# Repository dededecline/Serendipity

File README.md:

# Serendipity

## Board Details
Serendipity is a collaboration between [dededecline](https://github.com/dededecline) and [liv](https://github.com/ojthetiny)

Photos by group buy participants can be found [here!](https://imgur.com/a/I6LpYkj)

More info can be found on the [Geekhack interest check.](https://geekhack.org/index.php?topic=119558)

## Hardware
* **Back Case Screws:** [4x m3x14mm](https://www.mcmaster.com/92832A566)
* **Front Case Screws:** [4x m3x8mm](https://www.mcmaster.com/90991A113)
* **Weight Screws:** [2x m3x5mm countersunk](https://www.mcmaster.com/90236A118)
* **Plate Screws:** [8x m3x8mm](https://www.mcmaster.com/90991A113)
* **Badge Screws:** [2x m2x5mm](https://www.mcmaster.com/90236A103)
* **DB Screws:** [4x m2x5mm](https://www.mcmaster.com/90236A103)
* **O-Rings:** [16x 1.5mmx2.5mm, 70 duro recommended](https://www.theoringstore.com/store/index.php?main_page=product_info&products_id=1817)
* **Feet:** [2x Geonworks 60% feet](https://geon.works/products/feet-284)

## Additional Information
The o-rings *are required* for the build to work properly. For each plate screw, one o-ring goes between the top case piece and the plate, and another goes between the plate and the screw head. Do not overly tighten plate screws.

All files required for manufacturing are present in this repository.

All relevant information about the board should be in the Geekhack interest check.

## ***DISCLAIMER***
These components have been tested and confirmed to work properly. I am not liable for any issues stemming from usage of these files. Order at your own risk. Support will not be provided, but pull requests will be reviewed and possibly accepted.

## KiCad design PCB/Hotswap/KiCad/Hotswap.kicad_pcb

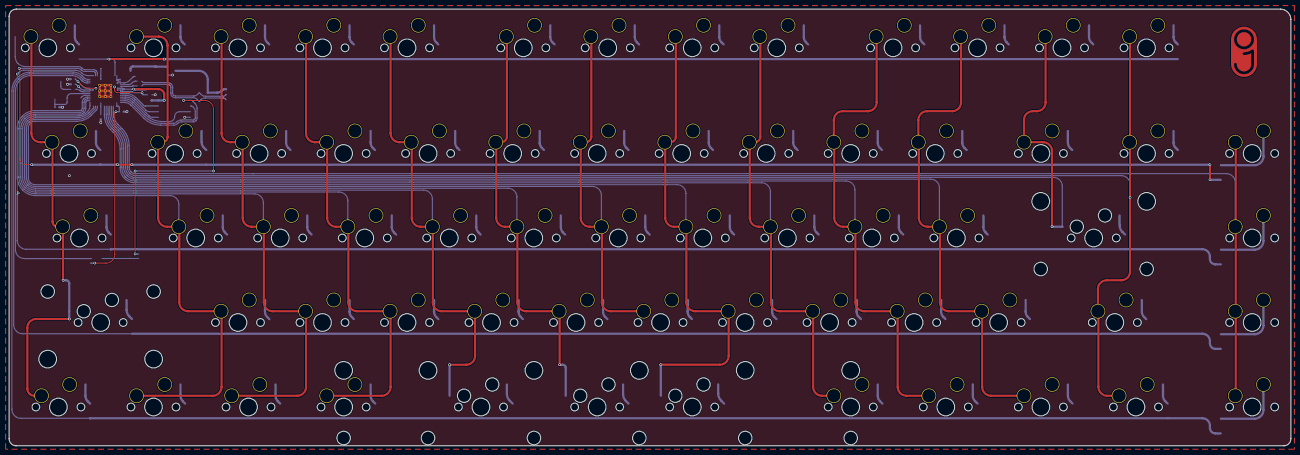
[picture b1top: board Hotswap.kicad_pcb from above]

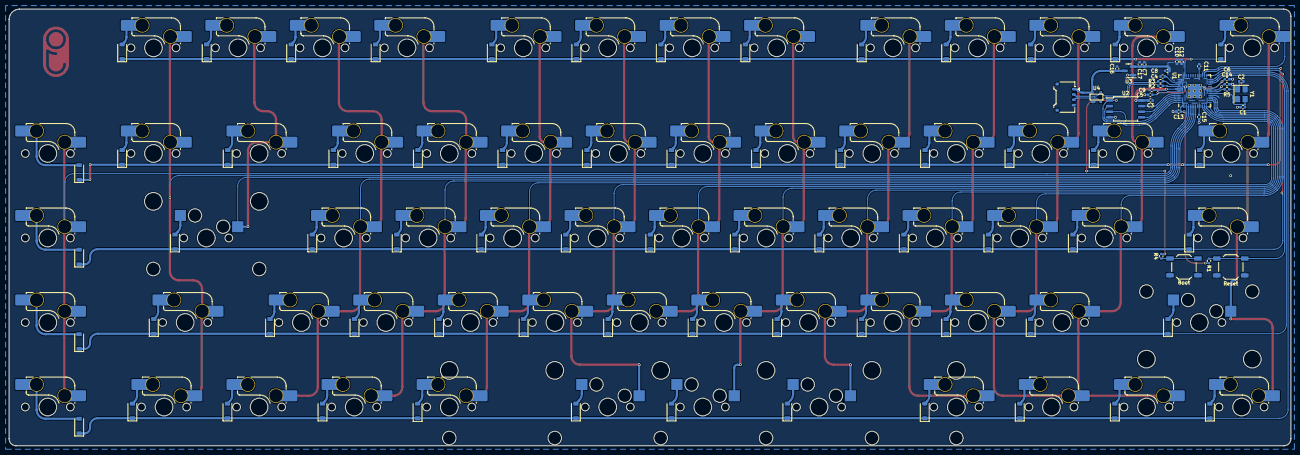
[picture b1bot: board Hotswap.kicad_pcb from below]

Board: 2 copper layers, 288.9 x 98.4 mm, 160 parts (155 on the bottom side), 103 nets.

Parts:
C1, C2: 22pF; C_0402_1005Metric
C3, C5, C6, C9, C10, C11, C12, C13, C14, C15: .1u; C_0402_1005Metric
C4, C8, C16, C17: 1u; C_0402_1005Metric
C7: 10u; C_0402_1005Metric
D1, D2, D3, D4, D5, D6, D7, D8, D9, D10, D11, D12, D13, D14, D15, D16, D17, D18, D19, D20, D21, D22, D23, D24, D25, D26, D27, D28, D29, D30, D31, D32, D33, D34, D35, D36, D37, D38, D39, D40, D41, D42, D43, D44, D45, D46, D47, D48, D49, D50, D51, D52, D53, D54, D55, D56, D57, D58, D59, D60, D61, D62, D63, D64, D65: D_Small; D_SOD-123
J1: EZmate; Molex_Pico-EZmate_78171-0004_1x04-1MP_P1.20mm_Vertical
MX1, MX3, MX7, MX8, MX9, MX10, MX11, MX12, MX13, MX14, MX15, MX16, MX18, MX19, MX20, MX21, MX22, MX23, MX24, MX25, MX27, MX28, MX29, MX30, MX33, MX34, MX35, MX36, MX37, MX38, MX39, MX40, MX42, MX43, MX44, MX45, MX46, MX47, MX48, MX49, MX52, MX53, MX54, MX55, MX56, MX57, MX61, MX65, MX66, MX67, MX68, MX69: MX-NoLED; SW_MX_HS_1u
MX2, MX60: MX-NoLED; SW_MX_HS_1.5u
MX4: MX-NoLED; MXOnly-2.25U-Hotswap
MX5, MX17, MX51, MX64: MX-NoLED; SW_MX_HS_1.25u
MX6, MX63: MX-NoLED; SW_MX_HS_1.75u
MX26, MX59: MX-NoLED; MXOnly-2.25U-Hotswap-ReversedStabilizers
MX31: MX-NoLED; MXOnly-7U-Hotswap-ReversedStabilizers
MX41: MX-NoLED; MXOnly-2.75U-Hotswap-ReversedStabilizers
R1, R4, R5: 1k; R_0402_1005Metric
R2, R3: 27; R_0402_1005Metric
SW1: Boot; SW_SPST_TL3342
SW2: Reset; SW_SPST_TL3342
U1: RP2040; RP2040-QFN-56
U2: W25Q128JVS; SOIC-8_5.23x5.23mm_P1.27mm
U3: XC6206PxxxMR; SOT-23
U4: PRTR5V0U2X; SOT143B
Y1: 12MHz; Crystal_SMD_3225-4Pin_3.2x2.5mm

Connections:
+1V1: C4.1, C5.1, C6.1, U1.23 (DVDD), U1.45 (VREG_VOUT), U1.50 (DVDD)
+3V3: C3.1, C7.1, C8.1, C9.1, C10.1, C11.1, C12.1, C13.1, C14.1, C15.1, C17.1, R1.1, U1.1 (IOVDD), U1.10 (IOVDD), U1.22 (IOVDD), U1.33 (IOVDD), U1.42 (IOVDD), U1.43 (ADC_AVDD), U1.44 (VREG_VIN), U1.48 (USB_VDD), U1.49 (IOVDD), U2.8 (VCC), U3.2 (VO)
+5V: C16.1, J1.1, U3.3 (VI), U4.4 (VCC)
CS: R4.2, U1.56 (QSPI_SS_N), U2.1 (~CS)
D+: J1.3, R2.1, U4.2 (IO1)
D-: J1.2, R3.1, U4.3 (IO2)
GND: C1.1, C2.1, C3.2, C4.2, C5.2, C6.2, C7.2, C8.2, C9.2, C10.2, C11.2, C12.2, C13.2, C14.2, C15.2, C16.2, C17.2, J1.4, SW1.1, SW2.2, U1.19 (TESTEN), U1.57 (GND), U2.4 (GND), U3.1 (GND), U4.1 (GND), Y1.2, Y1.4
unnamed: C2.2, R5.1, Y1.1
unnamed: D1.2 (A), MX1.2 (ROW)
unnamed: D2.2 (A), MX2.2 (ROW)
unnamed: D3.2 (A), MX4.2 (ROW)
unnamed: D4.2 (A), MX5.2 (ROW)
unnamed: D5.2 (A), MX6.2 (COL)
unnamed: D6.2 (A), MX7.2 (ROW)
unnamed: D7.2 (A), MX8.2 (ROW)
unnamed: D8.2 (A), MX9.2 (ROW)
unnamed: D9.2 (A), MX10.2 (ROW)
unnamed: D10.2 (A), MX11.2 (ROW)
unnamed: D11.2 (A), MX12.2 (ROW)
unnamed: D12.2 (A), MX13.2 (ROW)
unnamed: D13.2 (A), MX14.2 (ROW)
unnamed: D14.2 (A), MX15.2 (ROW)
unnamed: D15.2 (A), MX17.2 (COL)
unnamed: D16.2 (A), MX18.2 (ROW)
unnamed: D17.2 (A), MX19.2 (ROW)
unnamed: D18.2 (A), MX20.2 (ROW)
unnamed: D19.2 (A), MX21.2 (ROW)
unnamed: D20.2 (A), MX22.2 (ROW)
unnamed: D21.2 (A), MX23.2 (ROW)
unnamed: D22.2 (A), MX24.2 (ROW)
unnamed: D23.2 (A), MX25.2 (ROW)
unnamed: D24.2 (A), MX26.2 (ROW)
unnamed: D25.2 (A), MX27.2 (ROW)
unnamed: D26.2 (A), MX28.2 (ROW)
unnamed: D27.2 (A), MX29.2 (ROW)
unnamed: D28.2 (A), MX30.2 (ROW)
unnamed: D29.2 (A), MX31.2 (ROW)
unnamed: D30.2 (A), MX33.2 (ROW)
unnamed: D31.2 (A), MX34.2 (ROW)
unnamed: D32.2 (A), MX35.2 (ROW)
unnamed: D33.2 (A), MX36.2 (ROW)
unnamed: D34.2 (A), MX37.2 (ROW)
unnamed: D35.2 (A), MX38.2 (ROW)
unnamed: D36.2 (A), MX39.2 (ROW)
unnamed: D37.2 (A), MX40.2 (ROW)
unnamed: D38.2 (A), MX41.2 (ROW)
unnamed: D39.2 (A), MX42.2 (ROW)
unnamed: D40.2 (A), MX43.2 (ROW)
unnamed: D41.2 (A), MX44.2 (ROW)
unnamed: D42.2 (A), MX45.2 (ROW)
unnamed: D43.2 (A), MX46.2 (ROW)
unnamed: D44.2 (A), MX47.2 (ROW)
unnamed: D45.2 (A), MX48.2 (ROW)
unnamed: D46.2 (A), MX49.2 (ROW)
unnamed: D47.2 (A), MX51.2 (COL)
unnamed: D48.2 (A), MX52.2 (ROW)
unnamed: D49.2 (A), MX53.2 (ROW)
unnamed: D50.2 (A), MX54.2 (ROW)
unnamed: D51.2 (A), MX55.2 (ROW)
unnamed: D52.2 (A), MX56.2 (ROW)
unnamed: D53.2 (A), MX57.2 (ROW)
unnamed: D54.2 (A), MX59.2 (ROW)
unnamed: D55.2 (A), MX60.2 (COL)
unnamed: D56.2 (A), MX61.2 (ROW)
unnamed: D57.2 (A), MX63.2 (ROW)
unnamed: D58.2 (A), MX64.2 (ROW)
unnamed: D59.2 (A), MX65.2 (COL)
unnamed: D60.2 (A), MX66.2 (ROW)
unnamed: D61.2 (A), MX67.2 (ROW)
unnamed: D62.2 (A), MX68.2 (ROW)
unnamed: D63.2 (A), MX69.2 (ROW)
unnamed: D64.2 (A), MX3.2 (ROW)
unnamed: D65.2 (A), MX16.2 (COL)
unnamed: R4.1, SW1.2
unnamed: R2.2, U1.47 (D+)
unnamed: R3.2, U1.46 (D-)
QSPI_CLK: U1.52 (QSPI_SCLK), U2.6 (CLK)
RESET: R1.2, SW2.1, U1.26 (~RUN)
SD0: U1.53 (QSPI_SD0), U2.5 (DI(IO0))
SD1: U1.55 (QSPI_SD1), U2.2 (DO(IO1))
SD2: U1.54 (QSPI_SD2), U2.3 (IO2)
SD3: U1.51 (QSPI_SD3), U2.7 (IO3)
XTAL_IN: C1.2, U1.20 (XTAL_IN), Y1.3
XTAL_OUT: R5.2, U1.21 (XTAL_OUT)
col0: MX1.1 (COL), MX2.1 (COL), MX4.1 (COL), MX5.1 (COL), MX6.1 (ROW), U1.31 (GPIO20)
col1: MX7.1 (COL), MX8.1 (COL), MX9.1 (COL), MX10.1 (COL), MX11.1 (COL), U1.18 (GPIO15)
col2: MX12.1 (COL), MX13.1 (COL), MX14.1 (COL), MX15.1 (COL), MX17.1 (ROW), U1.17 (GPIO14)
col3: MX3.1 (COL), MX18.1 (COL), MX19.1 (COL), MX20.1 (COL), MX21.1 (COL), U1.16 (GPIO13)
col4: MX22.1 (COL), MX23.1 (COL), MX24.1 (COL), MX25.1 (COL), MX26.1 (COL), U1.15 (GPIO12)
col5: MX27.1 (COL), MX28.1 (COL), MX29.1 (COL), MX30.1 (COL), MX31.1 (COL), U1.14 (GPIO11)
col6: MX33.1 (COL), MX34.1 (COL), MX35.1 (COL), MX36.1 (COL), U1.13 (GPIO10)
col7: MX37.1 (COL), MX38.1 (COL), MX39.1 (COL), MX40.1 (COL), MX41.1 (COL), U1.12 (GPIO9)
col8: MX16.1 (ROW), MX42.1 (COL), MX43.1 (COL), MX44.1 (COL), MX45.1 (COL), U1.8 (GPIO6)
col9: MX46.1 (COL), MX47.1 (COL), MX48.1 (COL), MX49.1 (COL), MX51.1 (ROW), U1.7 (GPIO5)
col10: MX52.1 (COL), MX53.1 (COL), MX54.1 (COL), MX55.1 (COL), MX56.1 (COL), U1.6 (GPIO4)
col11: MX57.1 (COL), MX59.1 (COL), MX60.1 (ROW), U1.5 (GPIO3)
col12: MX61.1 (COL), MX63.1 (COL), MX64.1 (COL), MX65.1 (ROW), U1.4 (GPIO2)
col13: MX66.1 (COL), MX67.1 (COL), MX68.1 (COL), MX69.1 (COL), U1.3 (GPIO1)
row0: D1.1 (K), D6.1 (K), D11.1 (K), D16.1 (K), D20.1 (K), D25.1 (K), D30.1 (K), D34.1 (K), D39.1 (K), D43.1 (K), D48.1 (K), D53.1 (K), D56.1 (K), U1.41 (GPIO29/ADC3)
row1: D2.1 (K), D7.1 (K), D12.1 (K), D17.1 (K), D21.1 (K), D26.1 (K), D31.1 (K), D35.1 (K), D40.1 (K), D44.1 (K), D49.1 (K), D55.1 (K), D59.1 (K), D60.1 (K), U1.30 (GPIO19)
row2: D5.1 (K), D8.1 (K), D13.1 (K), D18.1 (K), D22.1 (K), D27.1 (K), D32.1 (K), D36.1 (K), D41.1 (K), D45.1 (K), D50.1 (K), D54.1 (K), D61.1 (K), U1.29 (GPIO18)
row3: D3.1 (K), D9.1 (K), D14.1 (K), D19.1 (K), D23.1 (K), D28.1 (K), D33.1 (K), D37.1 (K), D42.1 (K), D46.1 (K), D51.1 (K), D57.1 (K), D62.1 (K), U1.27 (GPIO16)
row4: D4.1 (K), D10.1 (K), D15.1 (K), D24.1 (K), D29.1 (K), D38.1 (K), D47.1 (K), D52.1 (K), D58.1 (K), D63.1 (K), D64.1 (K), D65.1 (K), U1.28 (GPIO17)

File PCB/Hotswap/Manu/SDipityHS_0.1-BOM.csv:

Comment,Designator,Footprint,LCSC
1k,"R1,R4,R5",R_0402_1005Metric,C11702
PRTR5V0U2X,U4,SOT143B,C12333
.1u,"C10,C11,C12,C13,C14,C15,C3,C5,C6,C9",C_0402_1005Metric,C1525
10u,C7,C_0402_1005Metric,C15525
22pF,"C1,C2",C_0402_1005Metric,C1555
RP2040,U1,RP2040-QFN-56,C2040
27,"R2,R3",R_0402_1005Metric,C25100
Boot,"SW1,SW2",SW_SPST_TL3342,C318884
MX-NoLED,"MX1,MX10,MX11,MX12,MX13,MX14,MX15,MX16,MX17,MX18,MX19,MX2,MX20,MX21,MX22,MX23,MX24,MX25,MX26,MX27,MX28,MX29,MX3,MX30,MX31,MX33,MX34,MX35,MX36,MX37,MX38,MX39,MX4,MX40,MX41,MX42,MX43,MX44,MX45,MX46,MX47,MX48,MX49,MX5,MX51,MX52,MX53,MX54,MX55,MX56,MX57,MX59,MX6,MX60,MX61,MX63,MX64,MX65,MX66,MX67,MX68,MX69,MX7,MX8,MX9",SW_MX_HS_1u,C5156480
1u,"C16,C17,C4,C8",C_0402_1005Metric,C52923
XC6206PxxxMR,U3,SOT-23,C5446
EZmate,J1,Molex_Pico-EZmate_78171-0004_1x04-1MP_P1.20mm_Vertical,C588524
D_Small,"D1,D10,D11,D12,D13,D14,D15,D16,D17,D18,D19,D2,D20,D21,D22,D23,D24,D25,D26,D27,D28,D29,D3,D30,D31,D32,D33,D34,D35,D36,D37,D38,D39,D4,D40,D41,D42,D43,D44,D45,D46,D47,D48,D49,D5,D50,D51,D52,D53,D54,D55,D56,D57,D58,D59,D6,D60,D61,D62,D63,D64,D65,D7,D8,D9",D_SOD-123,C64898
12MHz,Y1,Crystal_SMD_3225-4Pin_3.2x2.5mm,C9002
W25Q128JVS,U2,SOIC-8_5.23x5.23mm_P1.27mm,C97521

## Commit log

2024-02-15 format README
2024-02-15 mmmm feet
2024-02-15 Fix Thick Plate
    Remove a bit of material from the thick plate so the screws don't get pushed askew when installed
